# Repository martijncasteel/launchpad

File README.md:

# push-to-talk
A simple macro keyboard designed for using USB HID protocol.

> Unfortantly I was not able to get the device working as intended. There is nothing wrong with the hardware or the code, it is just something I want I can't do without getting a certification with Microsoft. I did learn a lot, plugging in a USB device will never be the same!

My approach is to use the USB HID protocol in full and specifically the USB HID Telephone pages. The goal is to mute and unmute the microphone on Teams on a laptop, even when teams is not in focus.

```
 BTN0  - flash, end call
 BTN1  - camera toggle on/off
 BTN2  - volume increment
 BTN3  - volume decrement
 BTN4  - volume mute
 BTN5  - microphone mute toggle
 BTN6  - Hold to unmute microphone
```

This repository contains the entire project, [/pcb](https://github.com/martijncasteel/launchpad/tree/main/pcb) contains the schematics and design of the board. I used [Kicad](https://www.kicad.org/) for this. The gerber files and other nessecities for manufacturing are located in the [/assembly](https://github.com/martijncasteel/launchpad/tree/main/assembly) folder.

The board is designed to have six regular 1u keycaps, and one 2u keycap. All use regular cherry mx key switches. The board has an ATmega32u4 with native usb support. The ICSP connector can be used to flash the microcontroller. 

The [software](https://github.com/martijncasteel/launchpad/tree/main/code) is written in C and built using avr-gcc. Using avrdude you can flash the microcontroller as well as setting some fuses. In my search on how other have done this, I haven't found a lot of sources on lowlevel programming with USB. To help you further along I added loads of comments. 

<br /><br /><!-- spacing for header -->

## My story so far
During my study I did a lot of software engineering but never went further than using arduino's. So my goal was to learn more about hardware. A lot of youtube videos brought me so far. [Ben Eater](https://youtu.be/wdgULBpRoXk) has some great videos explaining the USB protocol. [Mitch Davis](https://youtu.be/Q2DakPocvfs) goes into more detail about programming Atmega microcontrollers.

Using schematics from arduino I was able to create a schematic quite easily. Of course, also looked at the datasheets to have a better understanding.

After creating the [assembly](https://github.com/martijncasteel/launchpad/tree/main/assembly), I uploaded the files to a pcb manufactorer and also let them populate the board. I had some issues with the USB port since the wrong one was in the BOM. Finally I started [coding](https://github.com/martijncasteel/launchpad/tree/main/code), at first with the arduino IDE. But quickly realised that I wanted to do it from scratch. Down the rabbit hole, I went!

<br /><br /><!-- spacing for header -->

## Where I am now
Well, the hardware went back in a drawer, I'm updating my README and that's it I guess. The buttons declared in the normal consumer control are working; volume up/down, and mute. The toggle camera is somewhat working, however teams just freezes the last frame and is not able to recover from it. More about the implementation in the [code](https://github.com/martijncasteel/launchpad/tree/main/code) directory.

The buttons for the telephone page; mute microphone and flash are not working. The computer receives the commands fine but not actions is take by the OS or teams. It did cross my mind to implement it as a [generic keyboard](https://github.com/martijncasteel/launchpad/commit/3572334c3c04b70ffb8cd755422ddb2e0c5258f0) and use the teams shortcuts. The whole purpose was to be able to mute microsoft without having it in focus, so I scratched that idea. But it will work

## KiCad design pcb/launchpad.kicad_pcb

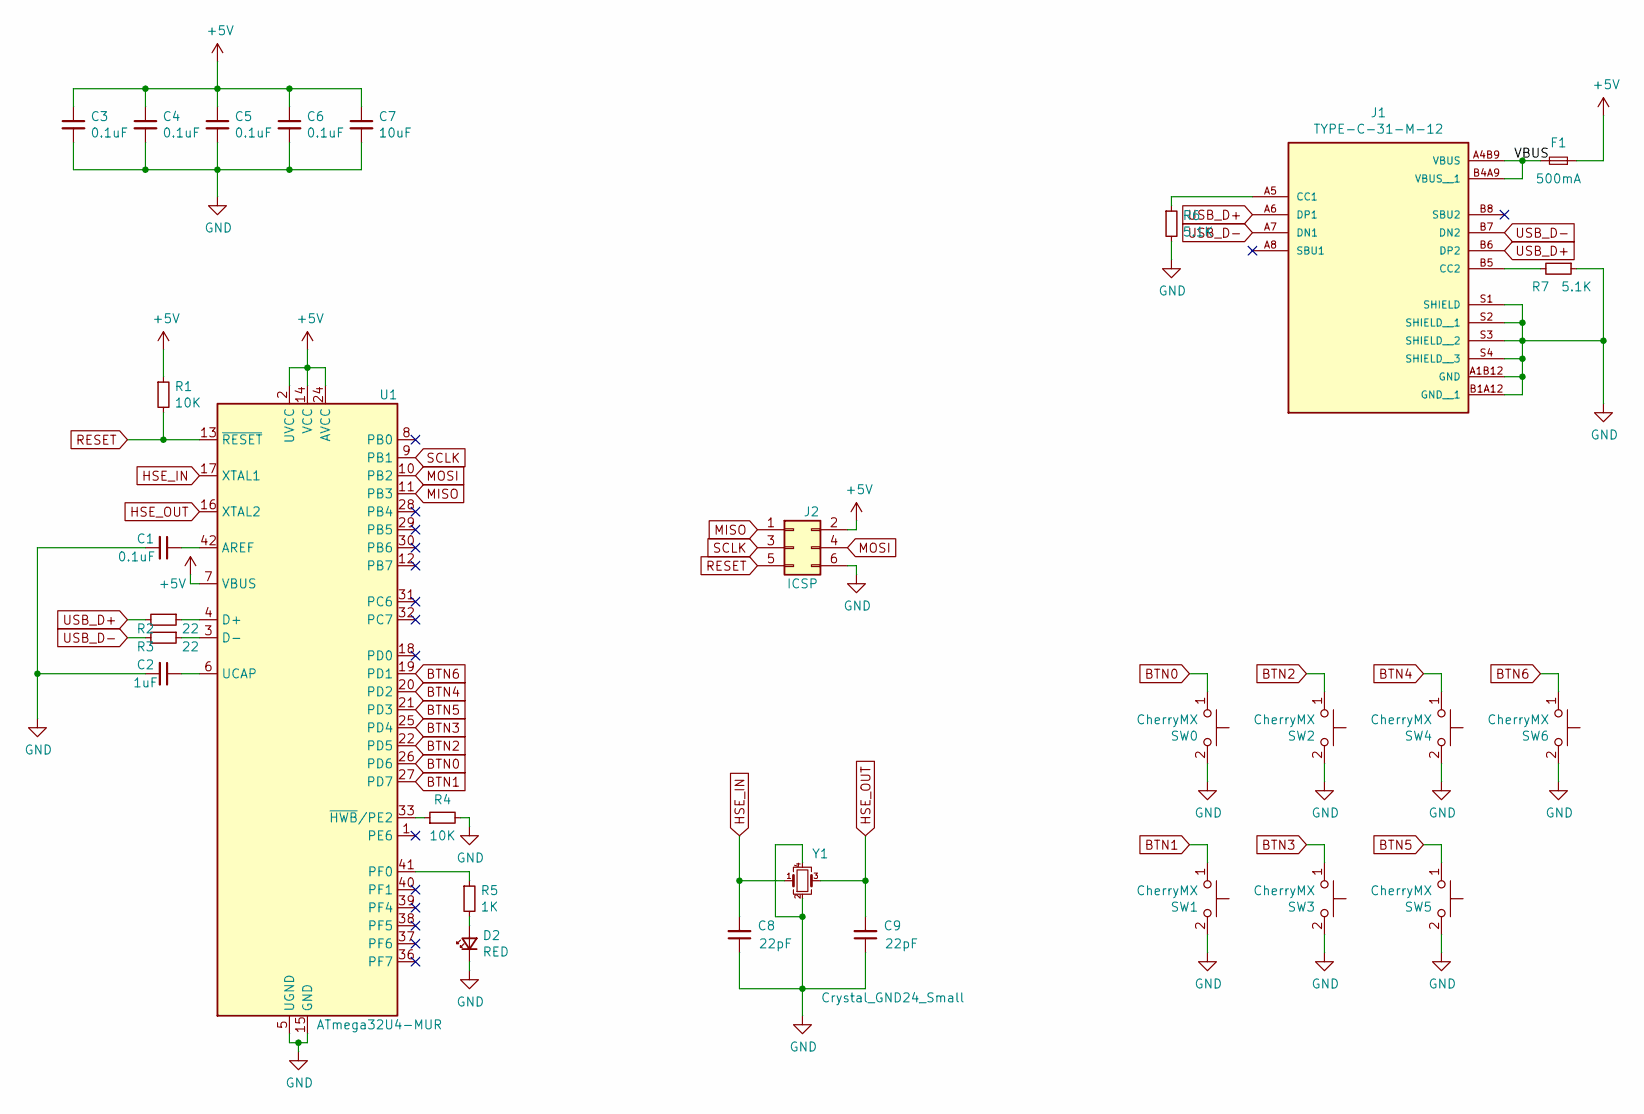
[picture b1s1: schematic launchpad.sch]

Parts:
C1, C3, C4, C5, C6: 0.1uF; C_0603_1608Metric; LCSC C14663
C2: 1uF; C_0603_1608Metric; LCSC C15849
C7: 10uF; C_0603_1608Metric; LCSC C19702
C8, C9: 22pF; C_0603_1608Metric; LCSC C1653
D2: RED; LED_0603_1608Metric; LCSC C2286
F1: 500mA; Fuse_0603_1608Metric; LCSC C261937
J1: TYPE-C-31-M-12; HRO_TYPE-C-31-M-12; PARTREV A; LCSC C165948
J2: ICSP; PinHeader_2x03_P2.54mm_Vertical
R1, R4: 10K; R_0603_1608Metric; LCSC C25804
R2, R3: 22; R_0603_1608Metric; LCSC C23345
R5: 1K; R_0603_1608Metric; LCSC C21190
R6, R7: 5.1K; R_0603_1608Metric; LCSC C23186
SW0, SW1, SW2, SW3, SW4, SW5: CherryMX; SW_Cherry_MX_1.00u_PCB
SW6: CherryMX; SW_Cherry_MX_2.00u_Vertical_PCB_unsupported
U1: ATmega32U4-MUR; QFN-44-1EP_7x7mm_P0.5mm_EP5.2x5.2mm; LCSC Part # C45874
Y1: Crystal_GND24_Small; Crystal_SMD_3225-4Pin_3.2x2.5mm; LCSC C13738

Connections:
+5V: C3.1, C4.1, C5.1, C6.1, C7.1, F1.1, J2.2, R1.1, U1.2 (UVCC), U1.7 (VBUS), U1.14 (VCC), U1.24 (AVCC), U1.34 (VCC), U1.44 (AVCC)
/VBUS: F1.2, J1.A4B9 (VBUS), J1.B4A9 (VBUS__1)
BTN0: SW0.1, U1.26 (PD6)
BTN1: SW1.1, U1.27 (PD7)
BTN2: SW2.1, U1.22 (PD5)
BTN3: SW3.1, U1.25 (PD4)
BTN4: SW4.1, U1.20 (PD2)
BTN5: SW5.1, U1.21 (PD3)
BTN6: SW6.1, U1.19 (PD1)
GND: C1.2, C2.2, C3.2, C4.2, C5.2, C6.2, C7.2, C8.1, C9.1, D2.1 (K), J1.A1B12 (GND), J1.B1A12 (GND__1), J1.S1 (SHIELD), J1.S2 (SHIELD__1), J1.S3 (SHIELD__2), J1.S4 (SHIELD__3), J2.6, R4.2, R6.2, R7.1, SW0.2, SW1.2, SW2.2, SW3.2, SW4.2, SW5.2, SW6.2, U1.5 (UGND), U1.15 (GND), U1.23 (GND), U1.35 (GND), U1.43 (GND), U1.45 (GND), Y1.2, Y1.4; also elsewhere on the board
HSE_IN: C8.2, U1.17 (XTAL1), Y1.1
HSE_OUT: C9.2, U1.16 (XTAL2), Y1.3
MISO: J2.1, U1.11 (PB3)
MOSI: J2.4, U1.10 (PB2)
unnamed: C1.1, U1.42 (AREF)
unnamed: C2.1, U1.6 (UCAP)
unnamed: D2.2 (A), R5.2
unnamed: J1.A5 (CC1), R6.1
unnamed: J1.B5 (CC2), R7.2
unnamed: R2.1, U1.4 (D+)
unnamed: R3.1, U1.3 (D-)
unnamed: R4.1, U1.33 (~HWB~/PE2)
unnamed: R5.1, U1.41 (PF0)
RESET: J2.5, R1.2, U1.13 (~RESET)
SCLK: J2.3, U1.9 (PB1)
USB_D+: J1.A6 (DP1), J1.B6 (DP2), R2.2
USB_D-: J1.A7 (DN1), J1.B7 (DN2), R3.2

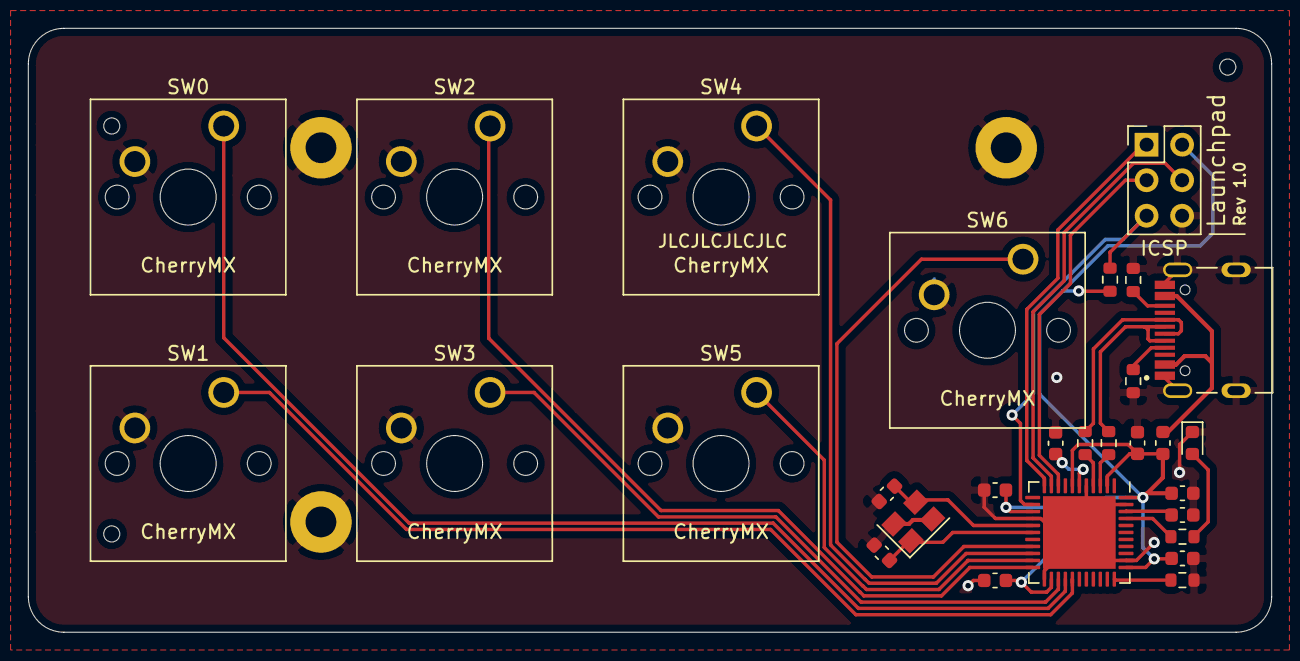
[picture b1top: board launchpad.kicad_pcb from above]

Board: 2 copper layers, 88.9 x 43.2 mm, 32 parts (0 on the bottom side), 27 nets.

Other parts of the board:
H1, H2, H3: MountingHole_Pad; MountingHole_2.2mm_M2_Pad

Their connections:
GND: H1.1, H2.1, H3.1; also elsewhere on the board

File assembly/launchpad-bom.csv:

Comment,Designator,Footprint,LCSC
"1uF","C2","Capacitor_SMD:C_0603_1608Metric","C15849"
"0.1uF","C1,C3,C4,C5,C6","Capacitor_SMD:C_0603_1608Metric","C14663"
"10uF","C7","Capacitor_SMD:C_0603_1608Metric","C19702 "
"22pF","C8,C9","Capacitor_SMD:C_0603_1608Metric","C1653"
"RED","D2","LED_SMD:LED_0603_1608Metric","C2286"
"500mA","F1","Fuse:Fuse_0603_1608Metric","C261937"
"TYPE-C-31-M-12","J1","Custom:HRO_TYPE-C-31-M-12","C165948"
"ICSP","J2","Connector_PinHeader_2.54mm:PinHeader_2x03_P2.54mm_Vertical",""
"22","R2,R3","Resistor_SMD:R_0603_1608Metric","C23345"
"10K","R1,R4","Resistor_SMD:R_0603_1608Metric","C25804"
"1K","R5","Resistor_SMD:R_0603_1608Metric","C21190"
"5.1K","R6,R7","Resistor_SMD:R_0603_1608Metric","C23186"
"CherryMX","SW0,SW1,SW2,SW3,SW4,SW5","Button_Switch_Keyboard:SW_Cherry_MX_1.00u_PCB",""
"CherryMX","SW6","Custom:SW_Cherry_MX_2.00u_Vertical_PCB_unsupported",""
"ATmega32U4-MUR","U1","Package_DFN_QFN:QFN-44-1EP_7x7mm_P0.5mm_EP5.2x5.2mm","C45874"
"Crystal_GND24_Small","Y1","Crystal:Crystal_SMD_3225-4Pin_3.2x2.5mm","C13738"

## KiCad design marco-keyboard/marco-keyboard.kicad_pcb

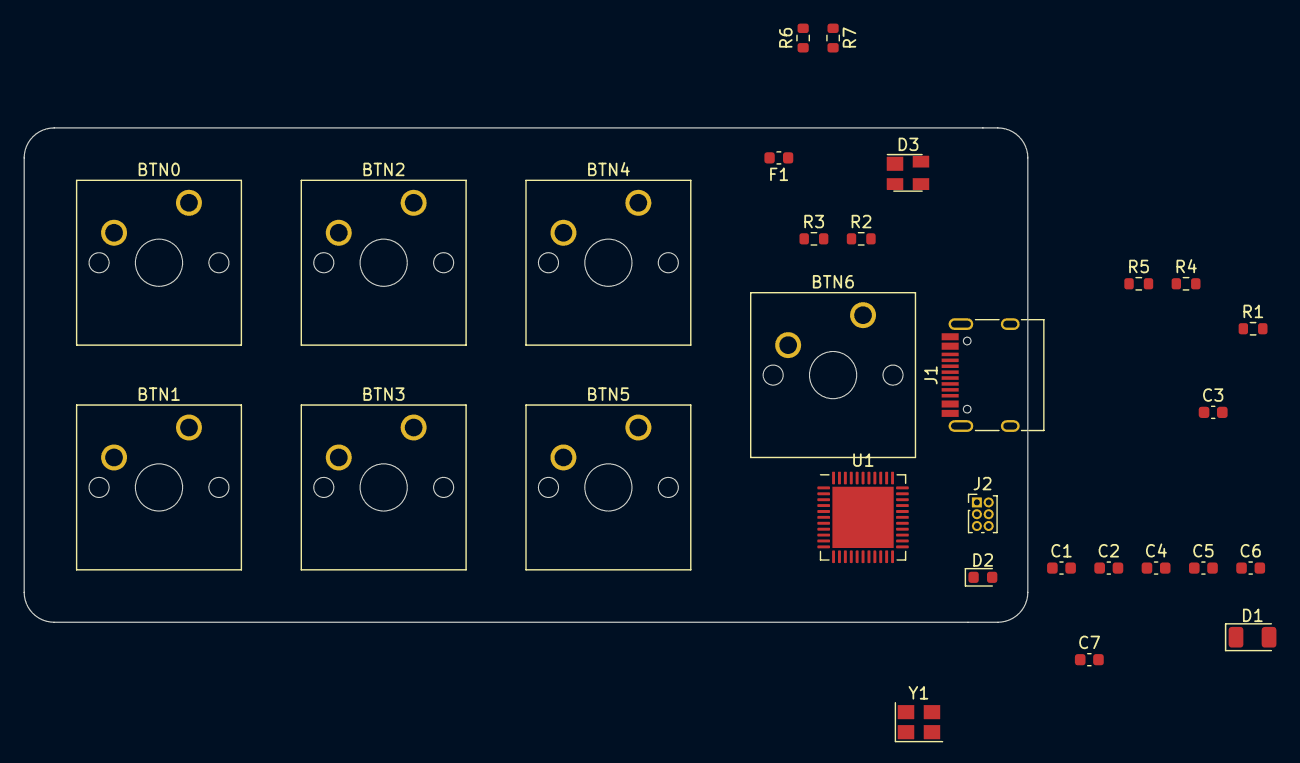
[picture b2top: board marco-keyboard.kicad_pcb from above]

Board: 2 copper layers, 85.1 x 41.9 mm, 29 parts (0 on the bottom side), 25 nets, no tracks yet.

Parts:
BTN0, BTN1, BTN2, BTN3, BTN4, BTN5, BTN6: CherryMX; SW_Cherry_MX_1.00u_PCB
C1: 10uF; C_0603_1608Metric
C2: 100nf; C_0603_1608Metric
C3: 1uF; C_0603_1608Metric
C4, C5: 0.1uF; C_0603_1608Metric
C6, C7: 22pF; C_0603_1608Metric
D1: D_Small; D_1206_3216Metric
D2: RED; LED_0603_1608Metric
D3: PRTR5V0U2X; SOT-143
F1: 500mA; Fuse_0603_1608Metric
J1: TYPE-C-31-M-12; USB_C_Receptacle_HRO_TYPE-C-31-M-12
J2: ICSP; PinHeader_2x03_P1.00mm_Vertical
R1, R4: 10K; R_0603_1608Metric
R2, R3: 22; R_0603_1608Metric
R5: 1K; R_0603_1608Metric
R6, R7: 5.1K; R_0603_1608Metric
U1: ATmega32U4-MUR; QFN-44-1EP_7x7mm_P0.5mm_EP5.2x5.2mm
Y1: X322516MLB4SI; Crystal_SMD_3225-4Pin_3.2x2.5mm

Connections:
BTN0: BTN0.1, U1.18
BTN1: BTN1.1, U1.19
BTN2: BTN2.1, U1.20
BTN3: BTN3.1, U1.21
BTN4: BTN4.1, U1.25
BTN5: BTN5.1, U1.22
BTN6: BTN6.1, U1.26
GND: C1.1, C2.1, C3.1, C4.2, C5.2, C6.1, C7.1, D2.1, D3.1, J2.6, R4.2, R6.2, R7.2, U1.5, U1.15, U1.23, U1.35, U1.43, U1.45, Y1.2, Y1.4
HSE_IN: C6.2, U1.17, Y1.3
HSE_OUT: C7.2, U1.16, Y1.1
MISO: J2.1, U1.11
MOSI: J2.4, U1.10
unnamed: C2.2, U1.42
unnamed: C3.2, U1.6
unnamed: D2.2, R5.2
unnamed: J1.A5, R6.1
unnamed: J1.B5, R7.1
unnamed: R2.1, U1.4
unnamed: R3.1, U1.3
unnamed: R4.1, U1.33
unnamed: R5.1, U1.8
RESET: D1.2, J2.5, R1.2, U1.13
USB_D+: D3.2, J1.A6, J1.B6, R2.2
USB_D-: D3.3, J1.A7, J1.B7, R3.2
UVCC: BTN0.2, BTN1.2, BTN2.2, BTN3.2, BTN4.2, BTN5.2, BTN6.2, C1.2, C4.1, C5.1, D1.1, D3.4, F1.1, J2.2, R1.1, U1.2, U1.7, U1.14, U1.24, U1.34, U1.44

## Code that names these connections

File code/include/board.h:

/**
 * @file board.h
 * @brief Header file contains the layout of the board
 * 
 * @author Martijn Casteel
 * @date 2022-12-22
*/

#include <avr/io.h>

#ifndef BOARD_H
#define BOARD_H

/**
 * Layout of the board, all buttons are connected to the D 
 * register (PORTD). Should have made this mapping way 
 * simpler, revision 2 perhaps?
 * 
 * There is a single led on PORTF0.
 * 
 *  +------+------+------+------+
 *  | BTN0 | BTN2 | BTN4 |      |
 *  +------+------+------+ BTN6 |
 *  | BTN1 | BTN3 | BTN5 |      |
 *  +------+------+------+------+
 * 
 */

#define BTN0 PIND6
#define BTN1 PIND7
#define BTN2 PIND5
#define BTN3 PIND4
#define BTN4 PIND2
#define BTN5 PIND3
#define BTN6 PIND1

/**
 * BTN0  - flash
 * BTN1  - camera toggle
 * BTN2  - volume increment
 * BTN3  - volume decrement
 * BTN4  - volume mute
 * BTN5  - microphone mute toggle
 * BTN6  - Hold to unmute microphone
 * 
 * PIND0 - 
 * PIND1 - hold to unmute microphone
 * PIND2 - volume mute
 * PIND3 - microphone mute toggle 
 * PIND4 - volume decrement
 * PIND5 - volume increment
 * PIND6 - flash
 * PIND7 - camera toggle 
 */

#define LED PORTF0

int8_t check_buttons(uint16_t* dout);
int8_t animate_led(uint8_t* din);

#endif

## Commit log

2021-03-03 Created a first schematic with ESD protection, might remove it
2021-03-20 Second version 0.2?
2021-03-21 First version almost done
2021-03-21 Created some files
2021-03-21 Fixed some things on the bom
2021-03-23 This looks like a good version
2021-03-24 So made the buttons active low. And found that I used the wrong ICSP header
2021-03-24 Updated pinheader to appropiate size
2021-03-25 Order is completed
2021-03-25 Added some ignored files
2022-11-07 kicad additional files
2022-11-19 Simple blink
2022-11-19 Fixed makefile
2022-11-20 Add properties for linux
2022-11-20 Added fuses to atleast use the external crystal at 16MHz
2022-12-26 A partial working control interface using USB. It's a start!
2022-12-26 Got string descriptors working! :)
2022-12-27 It sends letters! :D
2022-12-27 Bit of clean-up
2022-12-27 Added some comments, implemented VBUS interrupt
2022-12-28 Added config for mac
2022-12-29 Implemented logic for push-to-talk button, improved data register
2022-12-29 Added correct configuration for intellisense
2022-12-29 fixed a type-error
2022-12-29 received a pid from microchip
2022-12-29 Added PORT as a parameter for make, usage: make flash PORT=/dev/ttyUSB0
2023-01-15 Cannot debug because I only expanded ICSP no rx/tx for example
2023-05-06 Improved README.md
2023-05-06 Added a place for workaround using teams shortcuts
2023-05-06 Added readme to /code directory
2023-05-07 Described the button layout
2023-05-07 Created a first version with teams shortcuts, next testing
2023-05-14 Implemented a basic keyboard which happens to press teams shortcuts
2023-05-14 Renamed binary
2023-06-01 Another guy used a different endpoint address, lets try it
2023-06-03 Reverted endpoint address
2023-06-03 The keyboard works, volume not
2023-06-03 Pulled in updates from main
2023-06-04 Consumer controls work, let's focus on BTN6 next
2023-06-04 Moved some stuff around
2023-06-04 Moved init data to a logical place
2023-06-14 Started working on the LED page
2023-06-14 Updated readme's
2023-06-14 Added a photo
